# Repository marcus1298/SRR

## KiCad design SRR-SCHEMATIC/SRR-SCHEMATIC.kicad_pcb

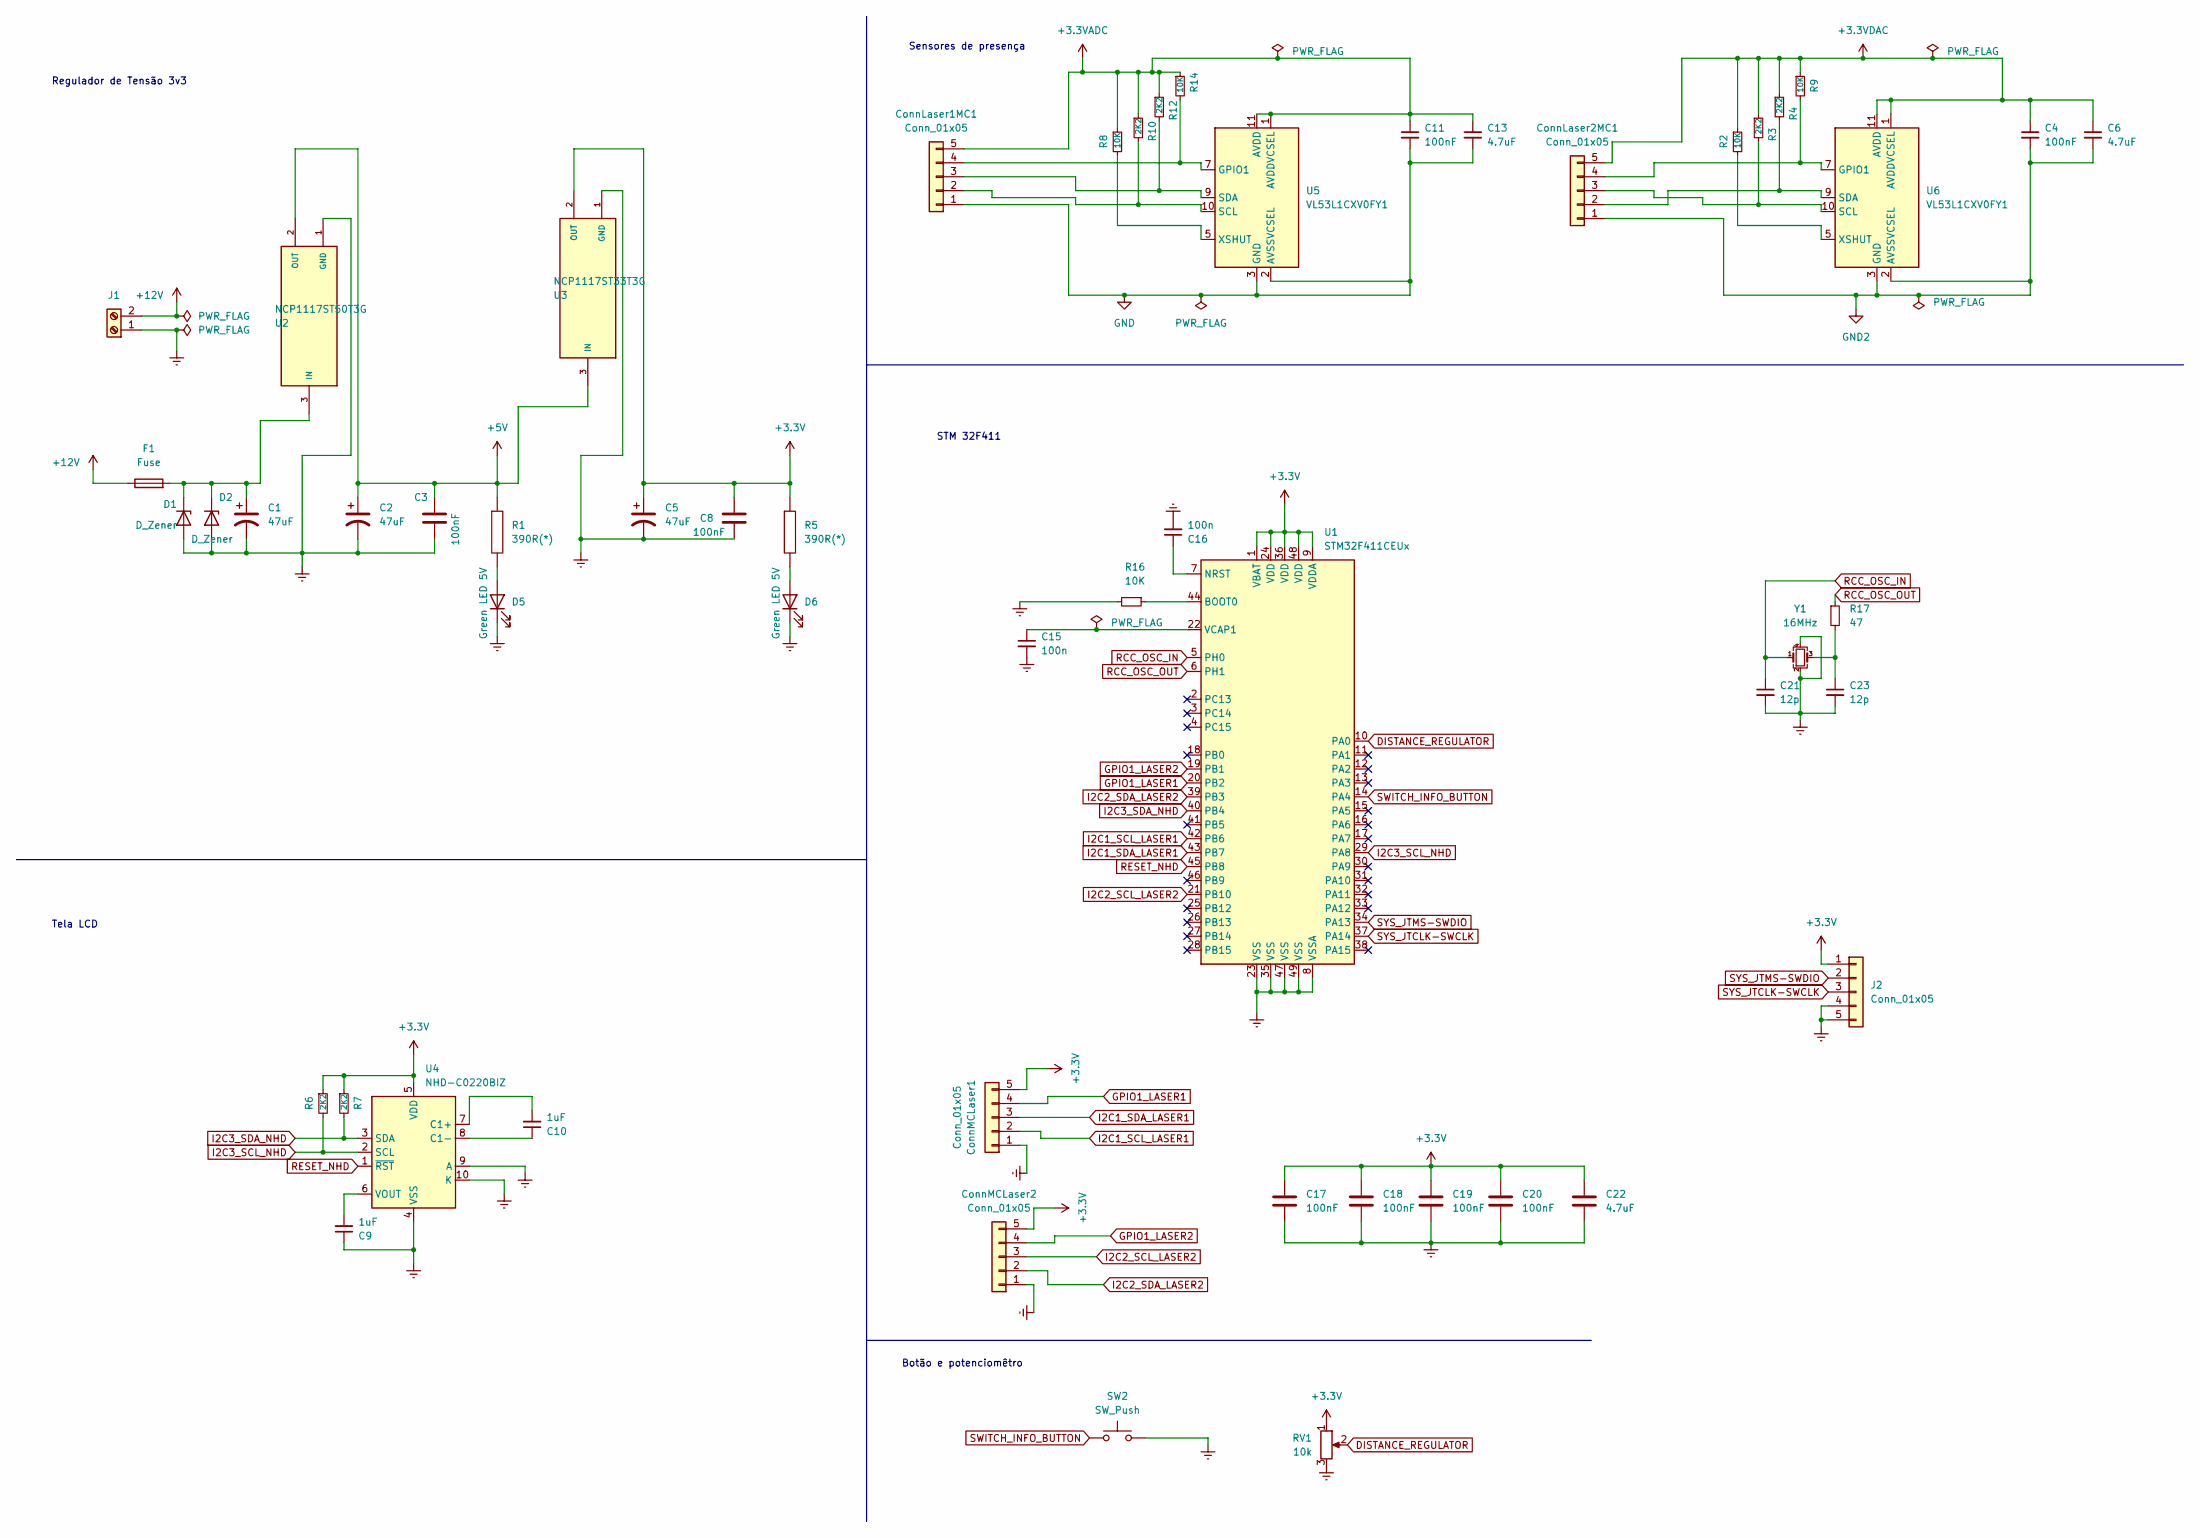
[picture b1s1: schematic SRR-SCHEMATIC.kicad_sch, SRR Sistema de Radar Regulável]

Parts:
C1, C2, C5: 47uF; C_0805_2012Metric
C3, C4, C8, C11: 100nF; C_0603_1608Metric
C6, C13, C22: 4.7uF; C_0603_1608Metric
C9, C10: 1uF; C_0603_1608Metric
C15, C16: 100n; C_0603_1608Metric
C17, C18, C19, C20: 100nF; C_0805_2012Metric
C21, C23: 12p; C_0603_1608Metric
ConnLaser1MC1, ConnLaser2MC1: Conn_01x05; PinHeader_1x05_P2.54mm_Vertical
ConnMCLaser1, ConnMCLaser2: Conn_01x05; PinHeader_1x05_P2.54mm_Vertical
D1, D2: D_Zener; D_0805_2012Metric
D5, D6: Green LED 5V; LED_D3.0mm
F1: Fuse; Fuse_0402_1005Metric
J1: Screw_Terminal_01x02; TerminalBlock_Phoenix_MKDS-1,5-2-5.08_1x02_P5.08mm_Horizont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
J2: Conn_01x05; PinHeader_1x05_P2.54mm_Vertical
R1, R5: 390R(*); R_0805_2012Metric
R2, R8, R9, R14, R16: 10K; R_0805_2012Metric
R3, R4, R6, R7, R10, R12: 2K2; R_0805_2012Metric
R17: 47; R_0603_1608Metric
RV1: 10k; Potentiometer_Bourns_3339P_Vertical_HandSoldering
SW2: SW_Push; SW_PUSH_6mm
U1: STM32F411CEUx; QFN-48-1EP_7x7mm_P0.5mm_EP5.6x5.6mm
U2: NCP1117ST50T3G; SOT230P700X180-4N
U3: NCP1117ST33T3G; SOT230P700X180-4N
U4: NHD-C0220BIZ; NHD-C0220BiZ
U5, U6: VL53L1CXV0FY1; ST_VL53L1x
Y1: 16MHz; Crystal_SMD_SeikoEpson_FA238-4Pin_3.2x2.5mm

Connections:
+3.3VADC: C11.1, C13.1, ConnLaser1MC1.5, R8.1, R10.1, R12.1, R14.1, U5.1 (AVDDVCSEL), U5.11 (AVDD); also elsewhere on the board
+3.3VDAC: C4.1, C6.1, ConnLaser2MC1.5, R2.1, R3.1, R4.1, R9.1, U6.1 (AVDDVCSEL), U6.11 (AVDD); also elsewhere on the board
+3V3: C5.1, C8.1, C17.1, C18.1, C19.1, C20.1, C22.1, ConnMCLaser1.5, ConnMCLaser2.5, J2.1, R5.1, R6.1, R7.1, RV1.1, U1.1 (VBAT), U1.9 (VDDA), U1.24 (VDD), U1.36 (VDD), U1.48 (VDD), U3.2 (OUT), U4.5 (VDD); also elsewhere on the board
+5V: C2.1, C3.1, R1.1, U2.2 (OUT), U3.3 (IN)
+12V: F1.1, J1.2
DISTANCE_REGULATOR: RV1.2, U1.10 (PA0)
GND: C11.2, C13.2, ConnLaser1MC1.1, U5.2 (AVSSVCSEL), U5.3 (GND), U5.4 (GND), U5.6 (GND), U5.12 (GND); also elsewhere on the board
GND2: C4.2, C6.2, ConnLaser2MC1.1, U6.2 (AVSSVCSEL), U6.3 (GND), U6.4 (GND), U6.6 (GND), U6.12 (GND); also elsewhere on the board
GNDREF: C1.2, C2.2, C3.2, C5.2, C8.2, C9.1, C15.2, C16.2, C17.2, C18.2, C19.2, C20.2, C21.2, C22.2, C23.2, ConnMCLaser1.1, ConnMCLaser2.1, D1.2 (A), D2.2 (A), D5.1 (K), D6.1 (K), J1.1, J2.4, J2.5, R16.2, RV1.3, SW2.2, U1.8 (VSSA), U1.23 (VSS), U1.35 (VSS), U1.47 (VSS), U1.49 (VSS), U2.1 (GND), U3.1 (GND), U4.4 (VSS), U4.9 (A), U4.10 (K), Y1.2, Y1.4; also elsewhere on the board
GPIO1_LASER1: ConnMCLaser1.4, U1.20 (PB2); also elsewhere on the board
GPIO1_LASER2: ConnMCLaser2.4, U1.19 (PB1); also elsewhere on the board
I2C1_SCL_LASER1: ConnMCLaser1.2, U1.42 (PB6); also elsewhere on the board
I2C1_SDA_LASER1: ConnMCLaser1.3, U1.43 (PB7); also elsewhere on the board
I2C2_SCL_LASER2: ConnMCLaser2.3, U1.21 (PB10); also elsewhere on the board
I2C2_SDA_LASER2: ConnMCLaser2.2, U1.39 (PB3); also elsewhere on the board
I2C3_SCL_NHD: R6.2, U1.29 (PA8), U4.2 (SCL)
I2C3_SDA_NHD: R7.2, U1.40 (PB4), U4.3 (SDA)
unnamed: C1.1, D1.1 (K), D2.1 (K), F1.2, U2.3 (IN)
unnamed: C9.2, U4.6 (VOUT)
unnamed: C10.1, U4.8 (C1-)
unnamed: C10.2, U4.7 (C1+)
unnamed: C15.1, U1.22 (VCAP1)
unnamed: C16.1, U1.7 (NRST)
unnamed: C23.1, R17.2, Y1.3
unnamed 24: ConnLaser1MC1.2, R10.2, U5.10 (SCL); also elsewhere on the board
unnamed 25: ConnLaser1MC1.3, R12.2, U5.9 (SDA); also elsewhere on the board
unnamed 26: ConnLaser1MC1.4, R14.2, U5.7 (GPIO1); also elsewhere on the board
unnamed 27: ConnLaser2MC1.2, R4.2, U6.9 (SDA); also elsewhere on the board
unnamed 28: ConnLaser2MC1.3, R3.2, U6.10 (SCL); also elsewhere on the board
unnamed 29: ConnLaser2MC1.4, R9.2, U6.7 (GPIO1); also elsewhere on the board
unnamed: D5.2 (A), R1.2
unnamed: D6.2 (A), R5.2
unnamed: R2.2, U6.5 (XSHUT)
unnamed: R8.2, U5.5 (XSHUT)
unnamed: R16.1, U1.44 (BOOT0)
RCC_OSC_IN: C21.1, U1.5 (PH0), Y1.1
RCC_OSC_OUT: R17.1, U1.6 (PH1)
RESET_NHD: U1.45 (PB8), U4.1 (~RST)
SWITCH_INFO_BUTTON: SW2.1, U1.14 (PA4)
SYS_JTCLK-SWCLK: J2.3, U1.37 (PA14); also elsewhere on the board
SYS_JTMS-SWDIO: J2.2, U1.34 (PA13); also elsewhere on the board

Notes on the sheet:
Tela LCD
Botão e potenciomêtro
Sensores de presença
STM 32F411
Regulador de Tensão 3v3

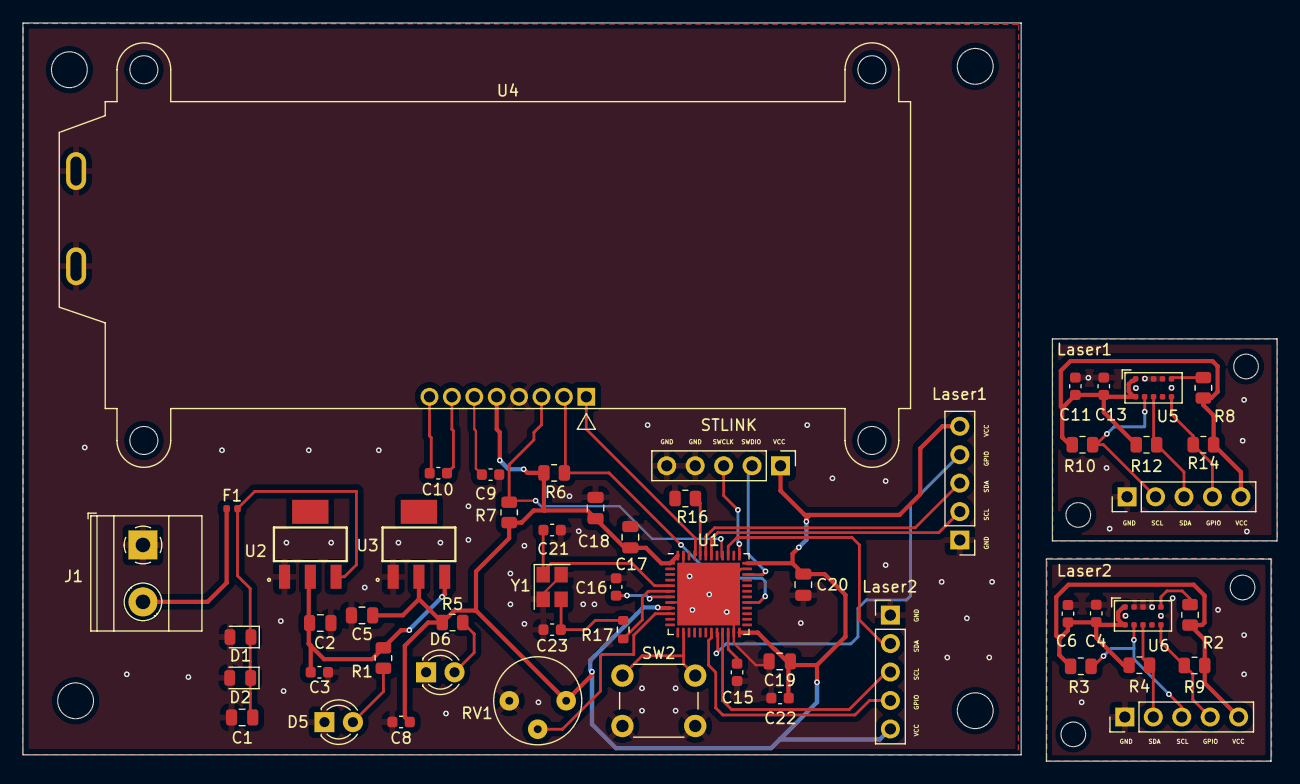
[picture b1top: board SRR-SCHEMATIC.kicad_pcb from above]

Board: 2 copper layers, 112.0 x 65.9 mm, 54 parts (0 on the bottom side), 41 nets.

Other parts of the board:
Laser1, Laser1#2, Laser2, Laser2#2: Conn_01x05; PinHeader_1x05_P2.54mm_Vertical
STLINK: Conn_01x05; PinHeader_1x05_P2.54mm_Vertical

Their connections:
+3.3VADC: Laser1#2.5; also elsewhere on the board
+3.3VDAC: Laser2.5; also elsewhere on the board
+3V3: Laser1.5, Laser2#2.5, STLINK.1; also elsewhere on the board
GND: Laser1#2.1; also elsewhere on the board
GND2: Laser2.1; also elsewhere on the board
GNDREF: Laser1.1, Laser2#2.1, STLINK.4, STLINK.5; also elsewhere on the board
GPIO1_LASER1: Laser1.4; also elsewhere on the board
GPIO1_LASER2: Laser2#2.4; also elsewhere on the board
I2C1_SCL_LASER1: Laser1.2; also elsewhere on the board
I2C1_SDA_LASER1: Laser1.3; also elsewhere on the board
I2C2_SCL_LASER2: Laser2#2.3; also elsewhere on the board
I2C2_SDA_LASER2: Laser2#2.2; also elsewhere on the board
unnamed 24: Laser1#2.2; also elsewhere on the board
unnamed 25: Laser1#2.3; also elsewhere on the board
unnamed 26: Laser1#2.4; also elsewhere on the board
unnamed 27: Laser2.2; also elsewhere on the board
unnamed 28: Laser2.3; also elsewhere on the board
unnamed 29: Laser2.4; also elsewhere on the board
SYS_JTCLK-SWCLK: STLINK.3; also elsewhere on the board
SYS_JTMS-SWDIO: STLINK.2; also elsewhere on the board

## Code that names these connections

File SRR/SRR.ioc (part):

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Mcu.Name=STM32F411C(C-E)Ux
Mcu.Package=UFQFPN48
Mcu.UserName=STM32F411CEUx
PA0-WKUP.GPIOParameters=GPIO_Label
PA0-WKUP.GPIO_Label=DISTANCE_REGULATOR
PA0-WKUP.Signal=ADCx_IN0
PA13.Mode=Serial_Wire
PA13.Signal=SYS_JTMS-SWDIO
PA14.Mode=Serial_Wire
PA14.Signal=SYS_JTCK-SWCLK
PA4.GPIOParameters=GPIO_PuPd,GPIO_Label,GPIO_ModeDefaultEXTI
PA4.GPIO_Label=SWITCH_INFO_BUTTON
PA4.GPIO_ModeDefaultEXTI=GPIO_MODE_IT_FALLING
PA4.GPIO_PuPd=GPIO_PULLUP
PA4.Signal=GPXTI4
PA8.GPIOParameters=GPIO_Label
PA8.GPIO_Label=I2C3_SCL_NHD
PA8.Mode=I2C
PA8.Signal=I2C3_SCL
PB1.GPIOParameters=GPIO_Label,GPIO_ModeDefaultEXTI
PB1.GPIO_Label=GPIO_LASER2
PB1.GPIO_ModeDefaultEXTI=GPIO_MODE_IT_FALLING
PB1.Signal=GPXTI1
PB10.GPIOParameters=GPIO_Label
PB10.GPIO_Label=I2C2_SCL_LASER2
PB10.Mode=I2C
PB10.Signal=I2C2_SCL
PB2.GPIOParameters=GPIO_Label,GPIO_ModeDefaultEXTI
PB2.GPIO_Label=GPIO_LASER1
PB2.GPIO_ModeDefaultEXTI=GPIO_MODE_IT_FALLING
PB2.Signal=GPXTI2
PB3.GPIOParameters=GPIO_Label
PB3.GPIO_Label=I2C2_SDA_LASER2
PB3.Mode=I2C
PB3.Signal=I2C2_SDA
PB4.GPIOParameters=GPIO_Label
PB4.GPIO_Label=I2C3_SDA_NHD
PB4.Mode=I2C
PB4.Signal=I2C3_SDA
PB6.GPIOParameters=GPIO_Label
PB6.GPIO_Label=I2C1_SLC_LASER1
PB6.Mode=I2C
PB6.Signal=I2C1_SCL
PB7.GPIOParameters=GPIO_Label
PB7.GPIO_Label=I2C1_SDA_LASER1
PB7.Mode=I2C
PB7.Signal=I2C1_SDA
PB8.GPIOParameters=GPIO_Label
PB8.GPIO_Label=RESET_NHD
PB8.Signal=GPIO_Output
PH0\ -\ OSC_IN.Mode=HSE-External-Oscillator
PH0\ -\ OSC_IN.Signal=RCC_OSC_IN
PH1\ -\ OSC_OUT.Mode=HSE-External-Oscillator
PH1\ -\ OSC_OUT.Signal=RCC_OSC_OUT
RCC.HSE_VALUE=16000000
RCC.SYSCLKFreq_VALUE=100000000
RCC.SYSCLKSource=RCC_SYSCLKSOURCE_PLLCLK
board=custom

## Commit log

2023-06-25 Subindo PCB
2023-06-25 Subindo o codigo
2023-06-25 Subindo codigo e PCB
2023-06-26 Subindo codigo atualizado
2023-06-26 Terminando codigo projeto
2023-06-26 Subindo PCB Corrigida
2023-06-26 Resolvendo warnings
2023-06-26 Subindo codigo
2023-06-26 PCB Final com Gerbers
2023-06-26 Fix warning uint status
2023-06-26 Alimentando a main
2023-06-27 Adicionando comentarios
